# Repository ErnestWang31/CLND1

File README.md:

# Closed-Loop Nema Driver
 Custom Closed-Loop Driver for Stepper Motors

### New Version:
- CAN Bus implementation, multiple motor daisy chaining, 4 wires connection
- FOC and PID algorithms
- In progress

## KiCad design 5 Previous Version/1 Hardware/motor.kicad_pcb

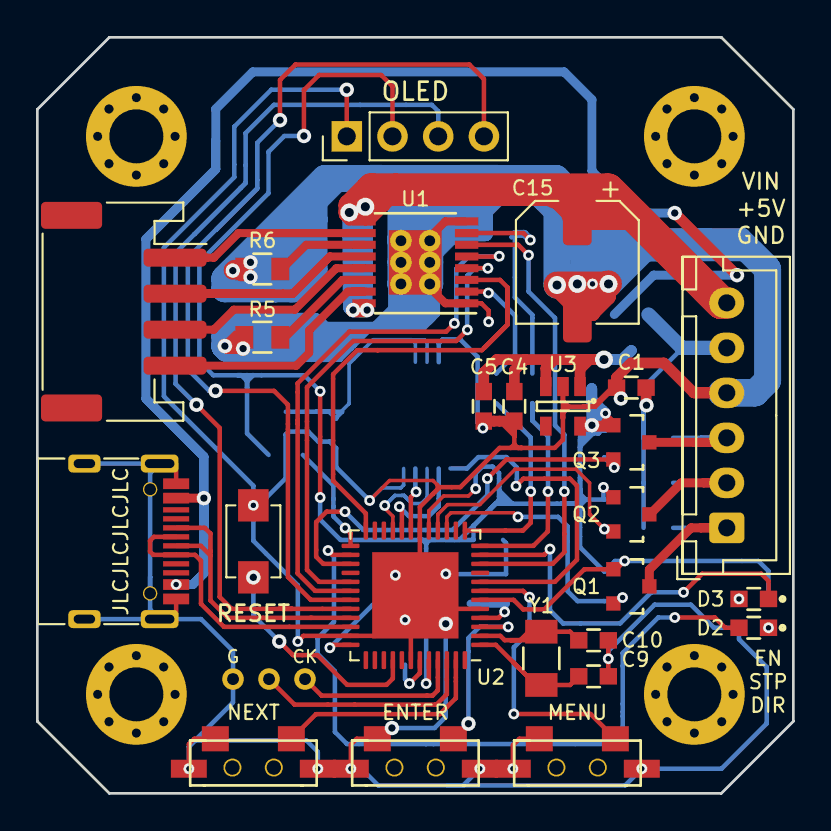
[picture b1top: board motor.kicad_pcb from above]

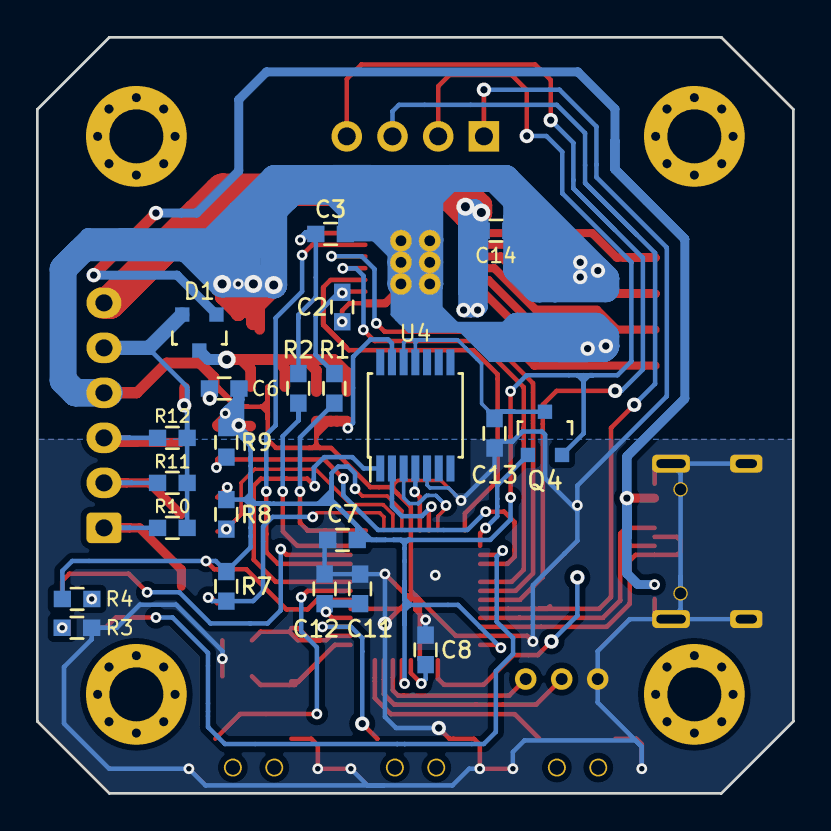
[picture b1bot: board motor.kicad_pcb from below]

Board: 2 copper layers, 42.0 x 42.0 mm, 52 parts (22 on the bottom side), 50 nets.

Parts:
C1, C2, C3, C4, C5, C6, C7, C11, C13, C14: 0.1uF; 0603_C
C8: 1uF; 0603_C
C9, C10: 10pF; 0603_C
C12: 4.7uF; 0603_C
C15: 100uF; CP_Elec_6.3x5.4_Nichicon
D1: BAT54C; SOT-23
D2, D3: LED; 0603_LED
J1: CONN_01X04; JST_PH_S4B-PH-SM4-TB_1x04-1MP_P2.00mm_Horizontal
J2: Conn_01x06_Male; JST_XH_B6B-XH-A_1x06_P2.50mm_Vertical
J3: CONN_01X04; PinHeader_1x04_P2.54mm_Vertical
P1: USB_C__USB2.0; USB-Type-C-NEW
P1#2, P1#3, P1#4, P1#5: CONN_1; O_5.6_3mm
P2: CONN_01X03; JLINK3
Q1, Q2, Q3: BSS138; SOT-23
Q4: AO3401A; SOT-23-L
R1, R2, R3, R4: 3.3K; 0603_R
R5, R6: 0.1R; 0805_R
R7, R8, R9, R10, R11, R12: 10K; 0603_R
SW1: ENTER; SWITCH_PUSH
SW2: MENU; SWITCH_PUSH
SW3: NEXT; SWITCH_PUSH
SW4: RESET; switchx3x4
U1: A4954; TSSOP-16-1EP_4.4x5mm_P0.65mm
U2: ATSAMD21G18A-MF; QFN-48-1EP_7x7mm_P0.5mm_ATSAMD21G18
U3: SPX3819; SOT23-5
U4: AS5047D; TSSOP-14_4.4x5mm_P0.65mm
Y1: 32.768KHz; OSC_32.768_Mini

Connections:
+3V3: C6.2, C7.2, J3.2, Q1.1, Q2.1, Q3.1, Q4.2, R4.2, R7.2, R8.2, R9.2, U2.6, U2.17, U2.36, U2.44, U3.5
/5V: C1.2, D1.2, J2.5, R10.2, R11.2, R12.2
/A0: SW1.2, U2.3
/A1: SW2.2, U2.7
/A2: U2.8, U4.1
/A4: U1.6, U2.10
/A5: SW3.2, U2.47
/AREF: C11.2, C12.2, U2.4
/D0: Q2.2, R8.1, U2.16
/D1: Q1.2, R7.1, U2.15
/D4: R1.2, U2.13
/D5: U1.3, U2.24
/D6: U1.4, U2.29
/D7: U1.5, U2.30
/D8: D3.1, U2.11
/D9: R2.2, U2.12
/D10: Q3.2, R9.1, U2.27
/D11: Q4.1, U2.25
/D13: D2.2, U2.26
/DIR: J2.1, Q1.3, R10.1
/EN: J2.3, Q3.3, R12.1
/MISO: U2.21, U4.3
/MOSI: U2.19, U4.4
/RESET: SW4.1, U2.40
/SCK: U2.20, U4.2
/SCL: J3.3, U2.32
/SDA: J3.4, U2.31
/STP: J2.2, Q2.3, R11.1
/SWCLK: P2.1, U2.45
/SWDIO: P2.2, U2.46
/VBUS: D1.1, P1.A4
/VIN: C14.2, C15.1, J2.6, U1.9, U1.16
GND: C1.1, C2.1, C3.1, C4.1, C5.1, C6.1, C7.1, C8.2, C9.1, C10.1, C11.1, C12.1, C13.1, C14.1, C15.2, J2.4, J3.1, P1.A1, P1.S1, P2.3, R3.2, R5.1, R6.1, SW1.1, SW2.1, SW3.1, SW4.2, U1.1, U1.8, U2.5, U2.18, U2.35, U2.42, U3.2, U4.5, U4.13
unnamed: C2.2, R1.1, U1.2
unnamed: C3.2, R2.1, U1.7
unnamed: C4.2, C5.2, D1.3, U3.1, U3.3
unnamed: C8.1, U2.43
unnamed: C9.2, U2.2, Y1.1
unnamed: C10.2, U2.1, Y1.2
unnamed: C13.2, Q4.3, U4.11, U4.12
unnamed: D2.1, R3.1
unnamed: D3.2, R4.1
unnamed: J1.1, U1.10
unnamed: J1.2, U1.12
unnamed: J1.3, U1.13
unnamed: J1.4, U1.15
unnamed: P1.A6, U2.34
unnamed: P1.A7, U2.33
unnamed: R5.2, U1.14
unnamed: R6.2, U1.11

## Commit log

2024-03-13 Hardware
2024-03-18 Version 2 Updates
2024-04-10 deleted controller dependent files, reconstructed
2024-04-10 small file changes
